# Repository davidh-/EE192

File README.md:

# Sp17_team1

Chris Berthelet,
David Domingez Hooper,
Nick Crispie

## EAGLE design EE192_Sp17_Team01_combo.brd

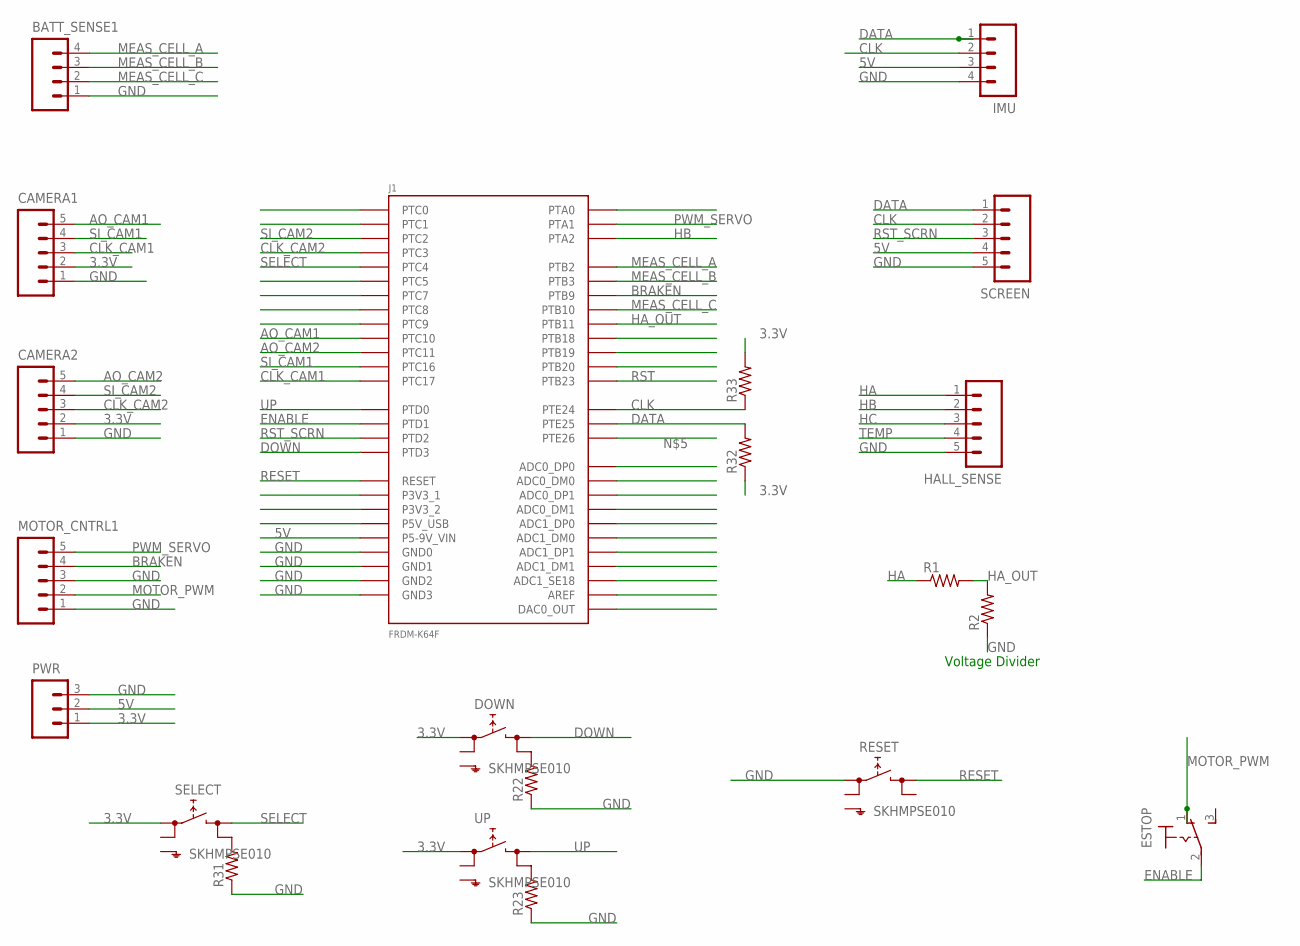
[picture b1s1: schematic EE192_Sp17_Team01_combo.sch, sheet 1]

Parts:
BATT_SENSE1: M041X04-MTA; 1X04-MTA
CAMERA1, CAMERA2: M05MTA; 1X05-MTA
DOWN: SKHMPSE010; SKHMPXE010
ESTOP: 320-916
HALL_SENSE: M05MTA; 1X05-MTA
IMU: M041X04-MTA; 1X04-MTA
J1: FRDM-K64F
MOTOR_CNTRL1: M05MTA; 1X05-MTA
PWR: M031X03-MTA; 1X03-MTA
R1, R2, R22, R23, R31, R32, R33: R-US_R0805; R0805
RESET: SKHMPSE010; SKHMPXE010
SCREEN: M05MTA; 1X05-MTA
SELECT: SKHMPSE010; SKHMPXE010
UP: SKHMPSE010; SKHMPXE010

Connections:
3.3V: CAMERA1.2, CAMERA2.2, DOWN.1 (1.1), PWR.1, R32.1, R33.2, SELECT.1 (1.1), UP.1 (1.1)
5V: IMU.3, J1.J3-16 (P5-9V_VIN), PWR.2, SCREEN.4
AO_CAM1: CAMERA1.5, J1.J4-12 (PTC10)
AO_CAM2: CAMERA2.5, J1.J4-10 (PTC11)
BRAKEN: J1.J1-6 (PTB9), MOTOR_CNTRL1.4; also elsewhere on the board
CLK: IMU.2, J1.J2-20 (PTE24), R33.1, SCREEN.2
CLK_CAM1: CAMERA1.3, J1.J1-4 (PTC17)
CLK_CAM2: CAMERA2.3, J1.J1-16 (PTC3)
DATA: IMU.1, J1.J2-18 (PTE25), R32.2, SCREEN.1
DOWN: DOWN.3 (2.1), J1.J2-10 (PTD3)
ENABLE: ESTOP.2, J1.J2-12 (PTD1); also elsewhere on the board
GND: BATT_SENSE1.1, CAMERA1.1, CAMERA2.1, HALL_SENSE.5, IMU.4, J1.J2-3 (GND0), J1.J2-14 (GND1), J1.J3-12 (GND2), J1.J3-14 (GND3), MOTOR_CNTRL1.1, MOTOR_CNTRL1.3, PWR.3, R2.1, R22.1, R23.1, R31.1, RESET.1 (1.1), SCREEN.5; also elsewhere on the board
HA: HALL_SENSE.1, R1.1; also elsewhere on the board
HA_OUT: J1.J4-8 (PTB11), R1.2, R2.2
HB: HALL_SENSE.2, J1.J1-12 (PTA2); also elsewhere on the board
HC: HALL_SENSE.3; also elsewhere on the board
MEAS_CELL_A: BATT_SENSE1.4, J1.J4-2 (PTB2); also elsewhere on the board
MEAS_CELL_B: BATT_SENSE1.3, J1.J4-4 (PTB3); also elsewhere on the board
MEAS_CELL_C: BATT_SENSE1.2, J1.J4-6 (PTB10); also elsewhere on the board
MOTOR_PWM: ESTOP.1 (O), MOTOR_CNTRL1.2
unnamed: R31.2, SELECT.4 (2.2)
unnamed: R23.2, UP.4 (2.2)
unnamed: DOWN.4 (2.2), R22.2
PWM_SERVO: J1.J1-8 (PTA1), MOTOR_CNTRL1.5; also elsewhere on the board
RESET: J1.J3-6 (RESET), RESET.3 (2.1)
RST: J1.J1-10 (PTB23)
RST_SCRN: J1.J2-8 (PTD2), SCREEN.3
SELECT: J1.J2-4 (PTC4), SELECT.3 (2.1)
SI_CAM1: CAMERA1.4, J1.J1-2 (PTC16)
SI_CAM2: CAMERA2.4, J1.J1-14 (PTC2)
TEMP: HALL_SENSE.4; also elsewhere on the board
UP: J1.J2-6 (PTD0), UP.3 (2.1)

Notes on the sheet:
Voltage Divider

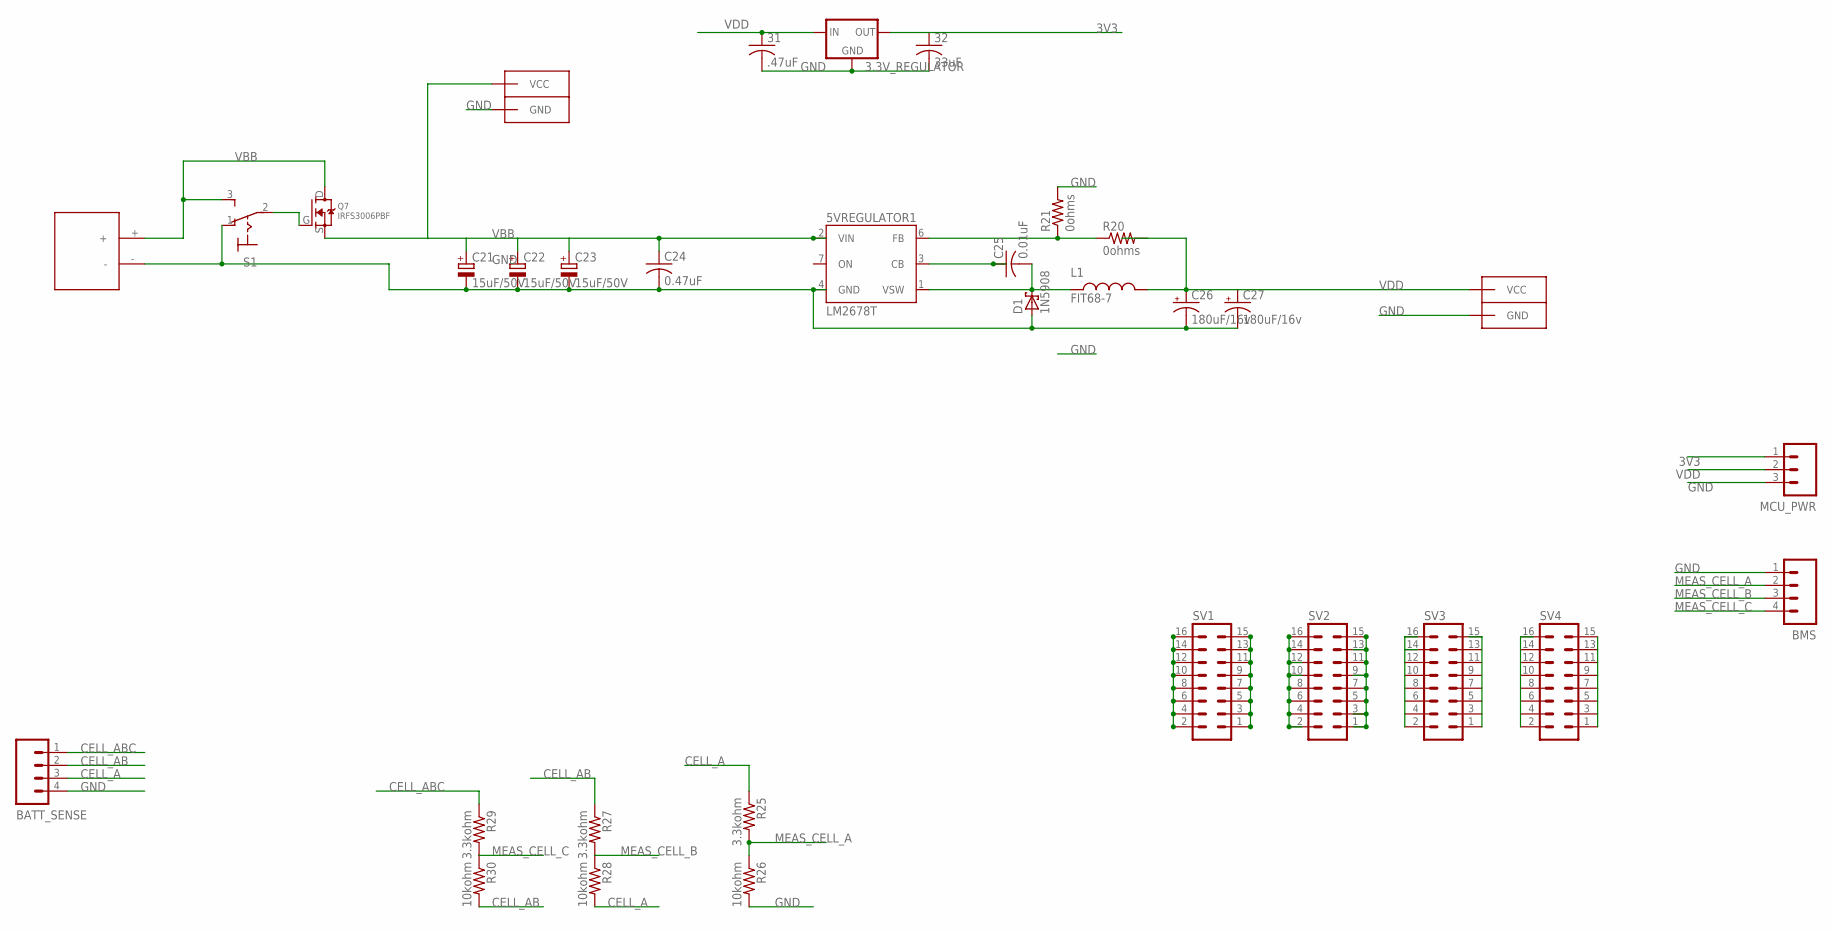
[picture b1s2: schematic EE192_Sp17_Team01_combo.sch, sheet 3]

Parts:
3.3V_REGULATOR: 78MXXL
5VREGULATOR1: LM2678T; TO220-7
31: .47uF; C0805
32: 33uF; C0805
BATT_SENSE: M041X04-MTA; 1X04-MTA
BMS: M041X04-MTA; 1X04-MTA
C21, C22, C23: 15uF/50V; CT7343
C24: 0.47uF; C0805
C25: 0.01uF; C0805
C26, C27: 180uF/16v; E3,5-8
CONN2: ANDERSON_PP_DOUBLEVERTICAL; ANDERSON_PP_DOUB_VERT
D1: 1N5908; C4111-15
L1: FIT68-7
MCU_PWR: M031X03-MTA; 1X03-MTA
MOTOR_PWR: ANDERSON_PP_DOUBLEVERTICAL; ANDERSON_PP_DOUB_VERT
Q7: IRFS3006PBF
R20, R21: 0ohms; R0805
R25, R27, R29: 3.3kohm; R0805
R26, R28, R30: 10kohm; R0805
S1: 320-916
SV1, SV2, SV3, SV4: MA08-2
U$5: TAMIYA

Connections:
3V3: 3.3V_REGULATOR.OUT, 32.1, MCU_PWR.1
CELL_A: BATT_SENSE.3, R25.1, R28.2
CELL_AB: BATT_SENSE.2, R27.1, R30.2
CELL_ABC: BATT_SENSE.1, R29.1
CONN_15_16: SV4.2, SV4.16
GND: 3.3V_REGULATOR.GND, 5VREGULATOR1.4 (GND), 31.2, 32.2, BATT_SENSE.4, BMS.1, C21.-, C22.-, C23.-, C24.2, C26.-, C27.-, CONN2.PIN1 (GND), D1.A, MCU_PWR.3, MOTOR_PWR.PIN1 (GND), R21.2, R26.2, S1.1 (O), U$5.-; also elsewhere on the board
MEAS_CELL_A: BMS.2, R25.2, R26.1; also elsewhere on the board
MEAS_CELL_B: BMS.3, R27.2, R28.1; also elsewhere on the board
MEAS_CELL_C: BMS.4, R29.2, R30.1; also elsewhere on the board
unnamed: 5VREGULATOR1.6 (FB), R20.1, R21.1
unnamed: SV2.1, SV2.3, SV2.5, SV2.7, SV2.9, SV2.11, SV2.13, SV2.15
unnamed: Q7.G, S1.2
unnamed: SV3.2, SV3.16
unnamed: SV3.1, SV3.15
unnamed: 5VREGULATOR1.3 (CB), C25.1
unnamed: SV2.2, SV2.4, SV2.6, SV2.8, SV2.10, SV2.12, SV2.14, SV2.16
unnamed: SV1.2, SV1.4, SV1.6, SV1.8, SV1.10, SV1.12, SV1.14, SV1.16
unnamed: SV1.1, SV1.3, SV1.5, SV1.7, SV1.9, SV1.11, SV1.13, SV1.15
unnamed: 5VREGULATOR1.1 (VSW), C25.2, D1.C, L1.P$1
unnamed: SV4.1, SV4.15
VBB: 5VREGULATOR1.2 (VIN), C21.+, C22.+, C23.+, C24.1, MOTOR_PWR.PIN2 (VCC), Q7.D, Q7.S, S1.3 (S), U$5.+; also elsewhere on the board
VDD: 3.3V_REGULATOR.IN, 31.1, C26.+, C27.+, CONN2.PIN2 (VCC), L1.P$2, MCU_PWR.2, R20.2; also elsewhere on the board

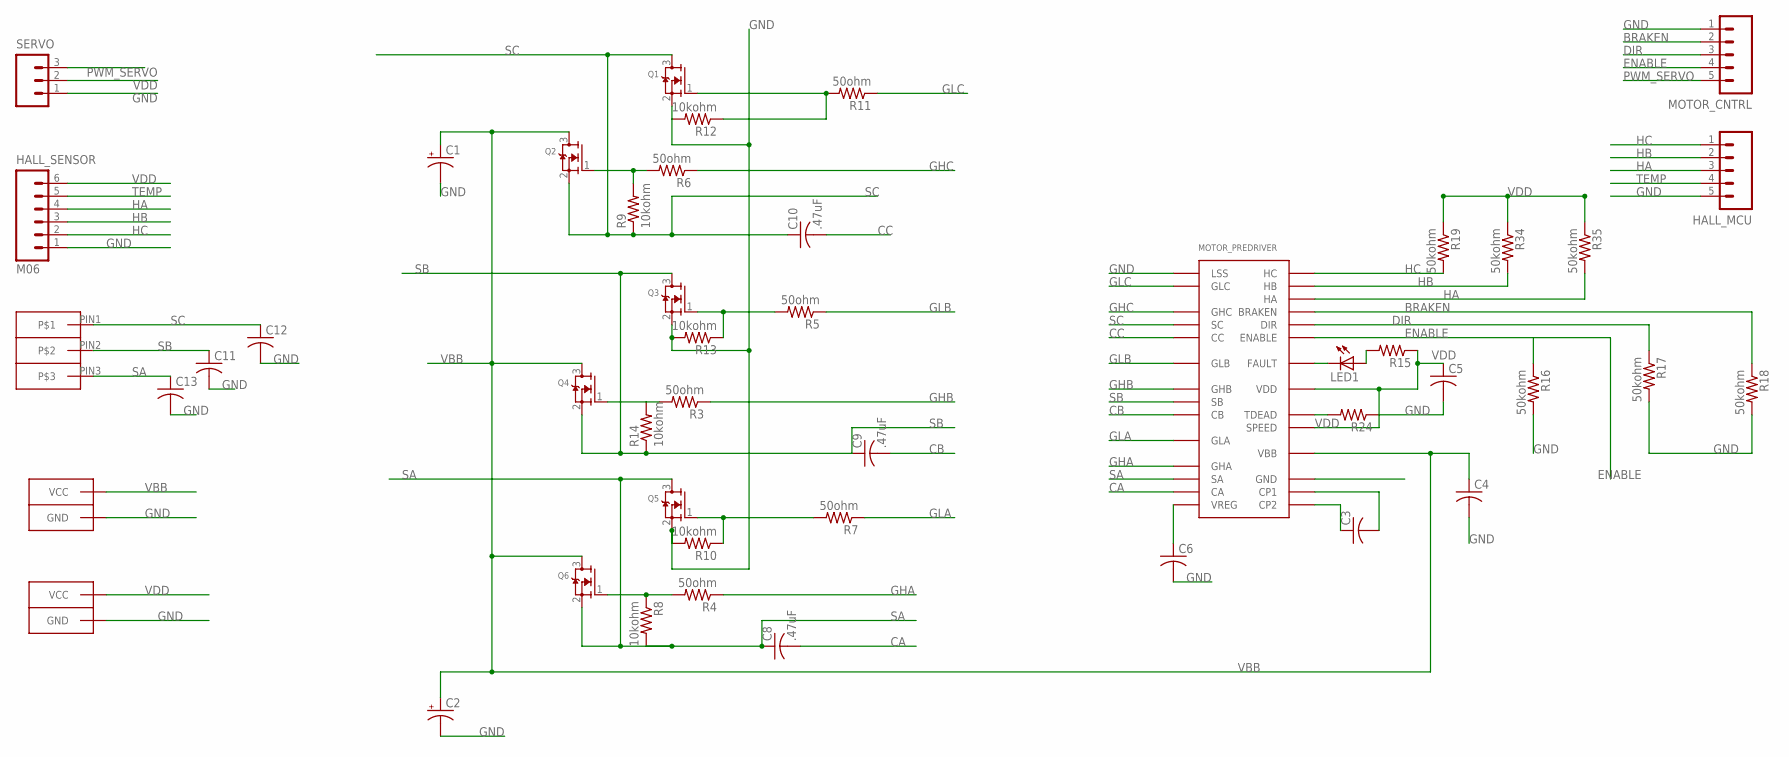
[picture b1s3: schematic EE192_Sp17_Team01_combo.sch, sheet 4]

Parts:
C1, C2: CPOL-USE5-10.5; E5-10,5
C3, C4, C5, C6, C11, C12, C13: C-USC0805; C0805
C8, C9, C10: .47uF; C0805
CONN1, CONN3: ANDERSON_PP_DOUBLEVERTICAL; ANDERSON_PP_DOUB_VERT
HALL_MCU: M05MTA; 1X05-MTA
HALL_SENSOR: M06; 1X06-MTA
LED1: LEDCHIPLED_0805; CHIPLED_0805
MOTOR_CNTRL: M05MTA; 1X05-MTA
MOTOR_PREDRIVER: A4915SOCKET; DIL28-6
MOTOR_PWR1: ANDERSON_PP_TRIPVERT; ANDERSON_PP_TRIP_VERT
Q1, Q2, Q3, Q4, Q5, Q6: IRFS3006PBFTO263PACKAGE; TO263
R3, R4, R5, R6, R7, R11: 50ohm; R0805
R8, R9, R10, R12, R13, R14: 10kohm; R0805
R15, R24: R-US_R0805; R0805
R16, R17, R18, R19, R34, R35: 50kohm; R0805
SERVO: M031X03-MTA; 1X03-MTA

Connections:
BRAKEN: MOTOR_CNTRL.2, MOTOR_PREDRIVER.25 (BRAKEN), R18.1; also elsewhere on the board
CA: C8.2, MOTOR_PREDRIVER.13 (CA)
CB: C9.2, MOTOR_PREDRIVER.9 (CB)
CC: C10.2, MOTOR_PREDRIVER.5 (CC)
DIR: MOTOR_CNTRL.3, MOTOR_PREDRIVER.24 (DIR), R17.1
ENABLE: MOTOR_CNTRL.4, MOTOR_PREDRIVER.23 (ENABLE), R16.1; also elsewhere on the board
GHA: MOTOR_PREDRIVER.11 (GHA), R4.1
GHB: MOTOR_PREDRIVER.7 (GHB), R3.1
GHC: MOTOR_PREDRIVER.3 (GHC), R6.1
GLA: MOTOR_PREDRIVER.10 (GLA), R7.1
GLB: MOTOR_PREDRIVER.6 (GLB), R5.1
GLC: MOTOR_PREDRIVER.2 (GLC), R11.1
GND: C1.-, C2.-, C4.2, C5.2, C6.2, C11.2, C12.2, C13.2, CONN1.PIN1 (GND), CONN3.PIN1 (GND), HALL_MCU.5, HALL_SENSOR.1, MOTOR_CNTRL.1, MOTOR_PREDRIVER.1 (LSS), Q1.2 (S), Q3.2 (S), Q5.2 (S), R10.2, R12.2, R13.2, R16.2, R17.2, R18.2, R24.1, SERVO.1; also elsewhere on the board
HA: HALL_MCU.3, HALL_SENSOR.4, MOTOR_PREDRIVER.26 (HA), R35.2; also elsewhere on the board
HB: HALL_MCU.2, HALL_SENSOR.3, MOTOR_PREDRIVER.27 (HB), R34.2; also elsewhere on the board
HC: HALL_MCU.1, HALL_SENSOR.2, MOTOR_PREDRIVER.28 (HC), R19.2; also elsewhere on the board
unnamed: C6.1, MOTOR_PREDRIVER.14 (VREG)
unnamed: Q6.1 (G), R4.2, R8.1
unnamed: Q2.1 (G), R6.2, R9.2
unnamed: Q3.1 (G), R5.2, R13.1
unnamed: Q4.1 (G), R3.2, R14.2
unnamed: Q5.1 (G), R7.2, R10.1
unnamed: MOTOR_PREDRIVER.20 (TDEAD), R24.2
unnamed: C3.1, MOTOR_PREDRIVER.15 (CP2)
unnamed: C3.2, MOTOR_PREDRIVER.16 (CP1)
unnamed: Q1.1 (G), R11.2, R12.1
unnamed: LED1.C, MOTOR_PREDRIVER.22 (FAULT)
unnamed: LED1.A, R15.2
PWM_SERVO: MOTOR_CNTRL.5, SERVO.3; also elsewhere on the board
SA: C8.1, C13.1, MOTOR_PREDRIVER.12 (SA), MOTOR_PWR1.PIN3, Q5.3 (D), Q6.2 (S), R8.2
SB: C9.1, C11.1, MOTOR_PREDRIVER.8 (SB), MOTOR_PWR1.PIN2, Q3.3 (D), Q4.2 (S), R14.1
SC: C10.1, C12.1, MOTOR_PREDRIVER.4 (SC), MOTOR_PWR1.PIN1, Q1.3 (D), Q2.2 (S), R9.1
TEMP: HALL_MCU.4, HALL_SENSOR.5; also elsewhere on the board
VBB: C1.+, C2.+, C4.1, CONN1.PIN2 (VCC), MOTOR_PREDRIVER.18 (VBB), Q2.3 (D), Q4.3 (D), Q6.3 (D); also elsewhere on the board
VDD: C5.1, CONN3.PIN2 (VCC), HALL_SENSOR.6, MOTOR_PREDRIVER.19 (SPEED), MOTOR_PREDRIVER.21 (VDD), R15.1, R19.1, R34.1, R35.1, SERVO.2; also elsewhere on the board

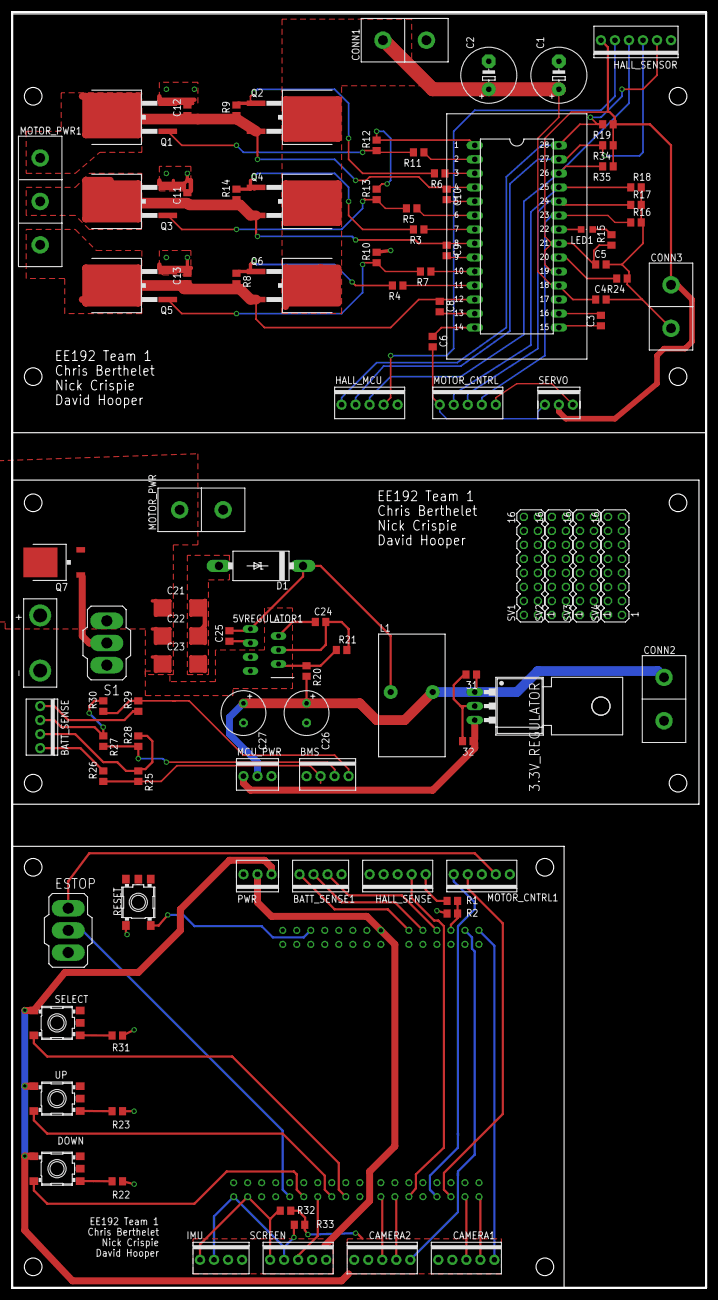
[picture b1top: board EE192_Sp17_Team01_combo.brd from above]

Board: 2 copper layers, 125.7 x 231.1 mm, 101 parts (1 on the bottom side), 74 nets.

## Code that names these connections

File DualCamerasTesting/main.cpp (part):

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

	//Fake ANALOG READ
	SI_CAM1 = 1;
	SI_CAM2 = 1;
	CLK_CAM1 = 1;
	CLK_CAM2 = 1;
	SI_CAM1 = 0;
	SI_CAM2 = 0;
	CLK_CAM1 = 0;
	CLK_CAM2 = 0;
	for(int i = 0; i < PIXELS; i++) {
		CLK_CAM1 = 1;
		CLK_CAM2 = 1;
		CLK_CAM1 = 0;
		CLK_CAM2 = 0;
	}

	wait(exp_time);
	SI_CAM1 = 1;
	SI_CAM2 = 1;
	CLK_CAM1 = 1;
	CLK_CAM2 = 1;
	SI_CAM1 = 0;
	SI_CAM2 = 0;
	data_cam1[0] = A0_CAM1.read_u16();
	CLK_CAM1 = 0;
	data_cam2[0] = A0_CAM2.read_u16();
	CLK_CAM2 = 0;

	for(int i = 1; i < PIXELS; i++) {


		CLK_CAM1 = 1;
		CLK_CAM2 = 1;
		data_cam1[i] = A0_CAM1.read_u16();
		data_cam2[i] = A0_CAM2.read_u16();

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			max_i_cam2 = i;
		}

		CLK_CAM1 = 0;
		CLK_CAM2 = 0;

		diff_cam1[i] = data_cam1[i] - prev_data_cam1[i];
		diff_cam2[i] = data_cam2[i] - prev_data_cam2[i];
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
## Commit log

2017-01-25 first commit, finished cp1
2017-01-25 added folder with work
2017-01-25 added team member names
2017-03-02 added code for checkpoint 6
2017-03-14 Adding preliminary velocity control code
2017-03-16 Upload EAGLE Files
    Add board schematics for combined motor driver and MCU shield
2017-03-16 added servo + motor + linecamera support. added bluetooth support, but lacks output (connects but no serial out)
2017-03-20 reworked cam code
2017-03-21 working state with no debug telem
2017-03-23 checkpoint 9 ready for demo
2017-03-23 added client files for telem
2017-03-23 added checkpoint submission files, also updated motor pwm duty cycle to 12%
2017-04-02 Adding first version of integrated steering+velocity code
2017-04-03 Add rev 2 boards
    Add rev 2 boards, update to MCU and power circuitry
2017-04-06 added cp10 code, includes rewritten camera read function, also exposure control is implemented
2017-04-06 updated to latest codebase
2017-04-07 checkpoint 10 ready code with 7% motor speed
2017-04-07 added submission files(waterfall plot)
2017-04-07 Adding cp10 code that was used in the checkoff
2017-04-09 First version of steering PD code
2017-04-10 add race1 files with steering PD control, camera exposure control, and steering logic when line is absent
2017-04-10 updated to include exposure control
2017-04-16 Adding folder with code that does double Hall velocity control with new MCU board
2017-04-18 Adding code that using new MCU and drives with fixed exposure time (does not have PD steering)
2017-04-20 2 cameras with linewidth calculation
2017-04-21 race 2 files with steering lock and 2 cameras for step tracking
2017-04-23 Adding the most current race2 code from 4/22 testing
2017-04-23 Adding code that ran the track at 24.2 seconds!
2017-04-24 update to latest code
2017-04-24 added fast analog in for cam0:PTB2, cam1:PTB3
